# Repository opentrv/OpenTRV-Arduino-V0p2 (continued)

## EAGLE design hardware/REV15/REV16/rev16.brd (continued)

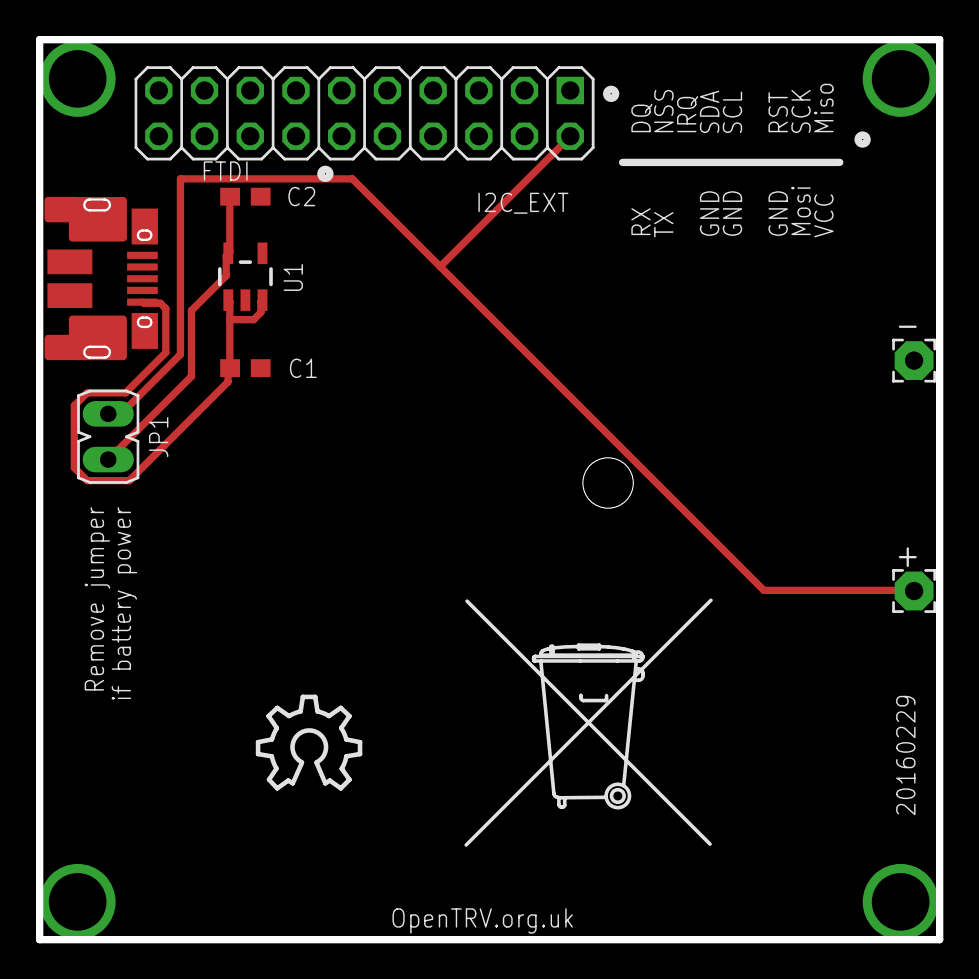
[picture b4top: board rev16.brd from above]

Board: 2 copper layers, 50.0 x 50.0 mm, 10 parts (0 on the bottom side), 4 nets.

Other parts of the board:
U$1: OSHW_10X200_NOTEXT
U$2: TONNE

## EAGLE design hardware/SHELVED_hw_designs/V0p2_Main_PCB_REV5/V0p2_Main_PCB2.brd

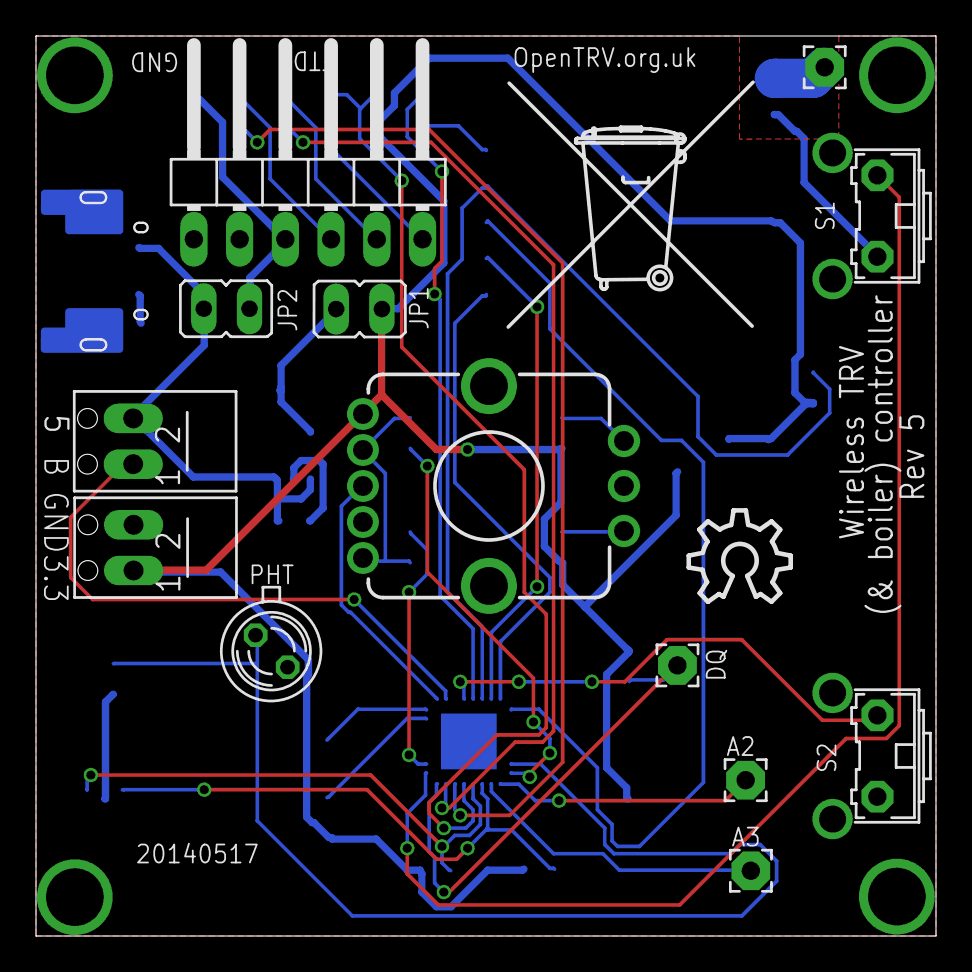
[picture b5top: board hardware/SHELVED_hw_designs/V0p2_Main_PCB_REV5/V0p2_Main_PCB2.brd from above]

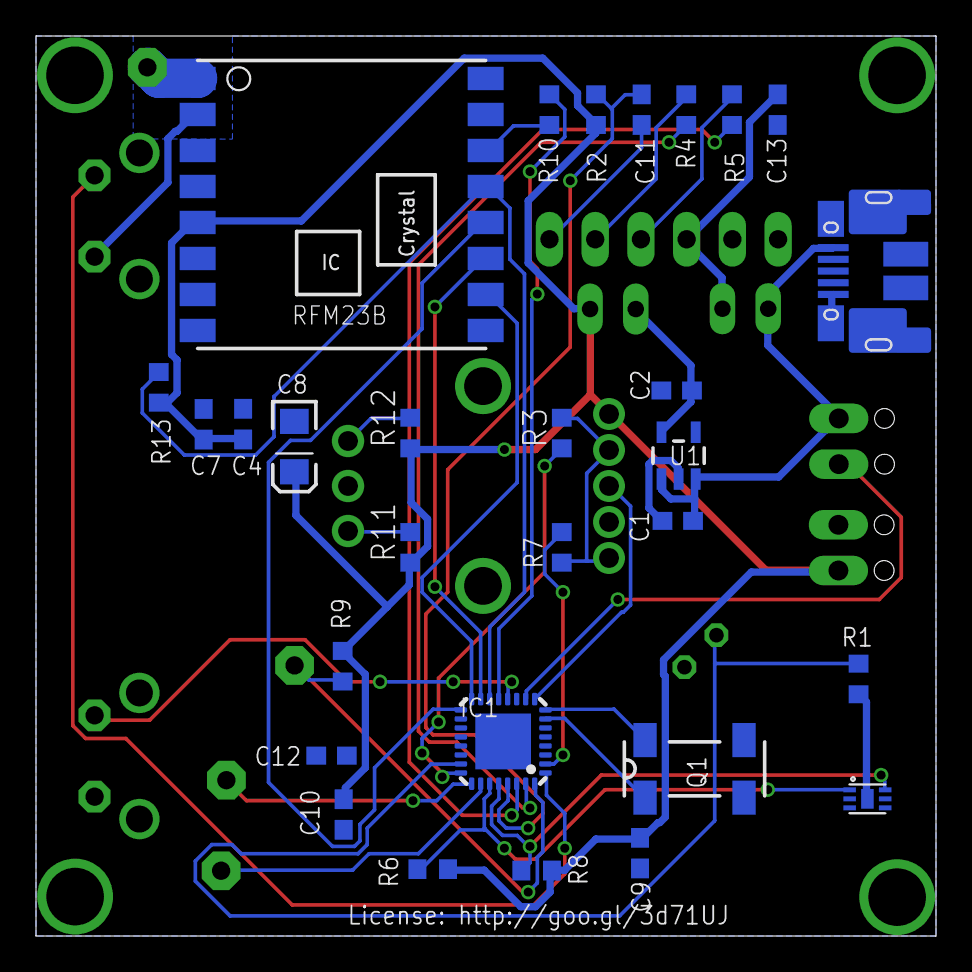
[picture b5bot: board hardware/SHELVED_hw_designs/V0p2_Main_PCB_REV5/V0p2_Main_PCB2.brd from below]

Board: 2 copper layers, 50.0 x 50.0 mm, 44 parts (29 on the bottom side), 37 nets.

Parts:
A2, A3: 2,15/1,0
ANT1: ANT (86 mm); 2,15/1,0
C1, C2, C13: 10uF 10V; C0603
C4: 100pF; C0603
C7, C9, C10, C11, C12: 100nF; C0603
C8: 100uF; EIA3216
DQ: 2,15/1,0
FTDI: 1X06/90
IC1: ATMEGA328-AU; MLF32
JP1, JP2: JP1
PHT: BPX65
Q1: 32768Hz; MC-306
R1: 100K; R0603
R2, R4, R5, R11, R12: 10K; R0603
R3, R7: 470R; R0603
R6, R8: 4K7; R0603
R9: 4.7K; R0603
R10: 1K; R0603
R13: 47K; R0603
RFM23B: RFM23B; RFM23-XXX-S1
S1, S2: B3F-31XX
SW1: ENCODER_LED_3
U1: TC1185SMD; TC1185
U$1: OSHW_10X200_NOTEXT
U$2: TONNE
U$4: SHT21
USBPOWER: MICRO-USB-FCI-10103592
X1, X2: SCREWTERMINAL

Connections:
5V: C1.1, JP2.2, U1.1, U1.3, USBPOWER.1, X1.2
BOILER: IC1.10, X1.1
BUTTON_LEARN2_L: IC1.1, S1.2
BUTTON_LEARN_L: IC1.12, S2.2
BUTTON_MODE_L: IC1.9, SW1.3
D2: DQ.1, IC1.32, R9.1
ENC_A: R11.2, SW1.A
ENC_B: R12.2, SW1.B
GND: C1.2, C2.1, C4.1, C7.2, C8.C, C9.2, C10.2, C12.2, C13.1, FTDI.1, FTDI.2, IC1.3, IC1.21, R1.2, RFM23B.2, RFM23B.9, RFM23B.15, RFM23B.16, S1.1, S2.1, SW1.C, U1.2, U$4.2, U$4.P$1, USBPOWER.5, USBPOWER.7, USBPOWER.17, X2.2
IO_POWER_UP: IC1.11, PHT.K
LDR: IC1.23, PHT.A, R1.1
LED_HEATCALL_B: IC1.24, R3.1
LED_HEATCALL_R: IC1.2, R7.1
unnamed: C11.2, FTDI.6
unnamed: FTDI.4, R5.2
unnamed: FTDI.5, R4.2
unnamed: C12.1, IC1.20
unnamed: R10.2, RFM23B.14
unnamed: C2.2, JP1.1, U1.5
unnamed: C13.2, FTDI.3, JP2.1
unnamed: R3.2, R7.2, SW1.1, SW1.4
unnamed: A2.1, IC1.25
unnamed: A3.1, IC1.26
unnamed: ANT1.1, RFM23B.1
RESET: C11.1, IC1.29, R2.2
RFM_IRQ: IC1.13, R10.1
RX: IC1.31, R4.1
SCL: IC1.28, R8.1, U$4.6
SDA: IC1.27, R6.2, U$4.1
SPI_MISO: IC1.16, RFM23B.10
SPI_MOSI: IC1.15, RFM23B.11
SPI_NSS: IC1.14, R13.1, RFM23B.13
SPI_SCK: IC1.17, RFM23B.12
TX: IC1.30, R5.1
VCC: C4.2, C7.1, C8.A, C9.1, C10.1, IC1.4, IC1.18, JP1.2, R2.1, R6.1, R8.2, R9.2, R11.1, R12.1, R13.2, RFM23B.5, SW1.5, U$4.5, X2.1
XTAL1: IC1.7, Q1.1
XTAL2: IC1.8, Q1.4

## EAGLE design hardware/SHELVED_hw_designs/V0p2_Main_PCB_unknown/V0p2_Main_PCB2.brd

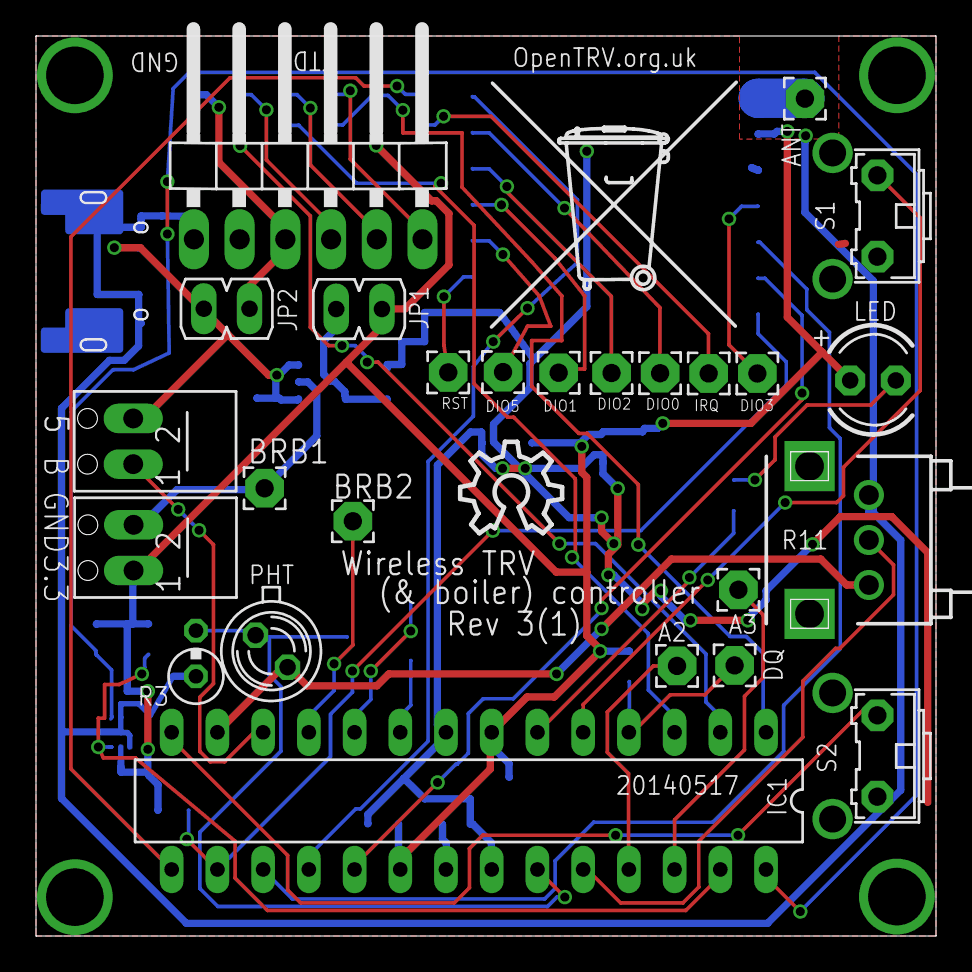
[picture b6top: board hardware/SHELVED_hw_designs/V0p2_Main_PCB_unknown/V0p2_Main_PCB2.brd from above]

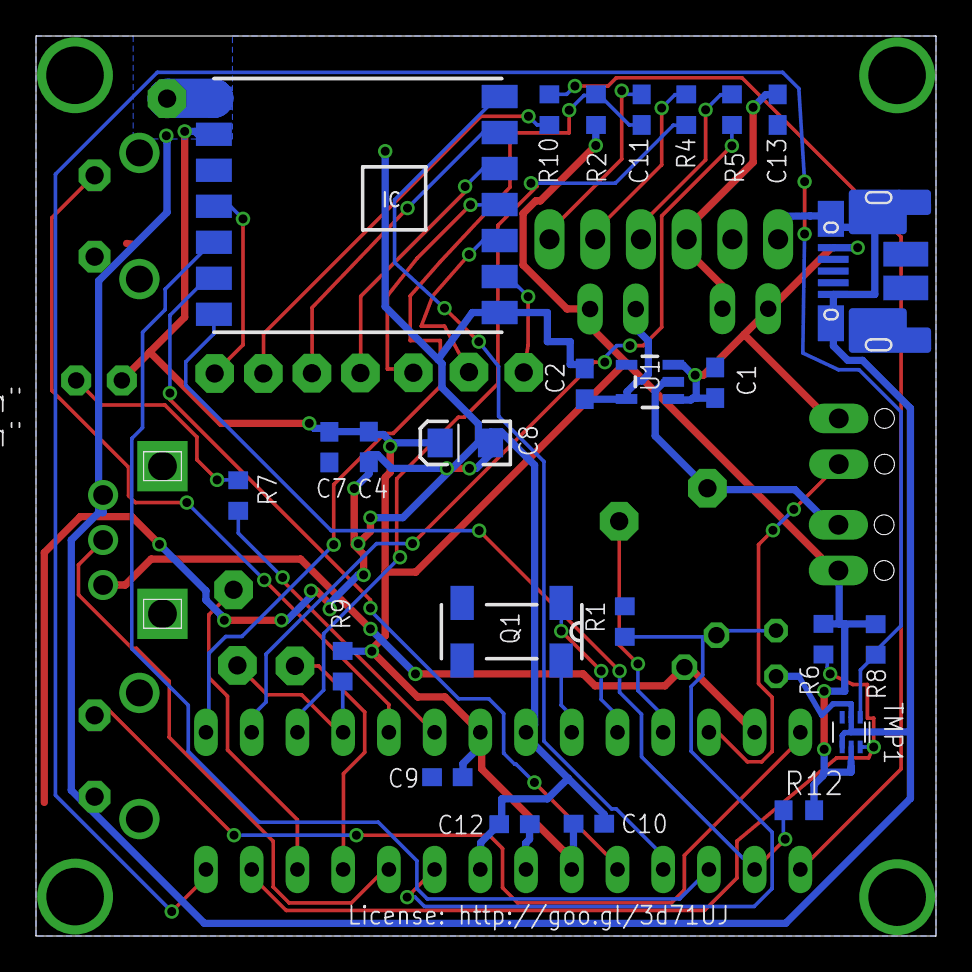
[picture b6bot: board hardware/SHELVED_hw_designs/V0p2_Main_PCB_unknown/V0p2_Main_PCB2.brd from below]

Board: 2 copper layers, 50.0 x 50.0 mm, 52 parts (25 on the bottom side), 41 nets.

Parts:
A2, A3: 2,15/1,0
ANT: ANT (86 mm); 2,15/1,0
BRB1: BRB1; 2,15/1,0
BRB2: BRB2; 2,15/1,0
C1, C2, C13: 10uF 10V; C0603
C4: 100pF; C0603
C7, C9, C10, C11, C12: 100nF; C0603
C8: 100uF; EIA3216
DIO0, DIO1, DIO2, DIO3, DIO5: ANT (86 mm); 2,15/1,0
DQ: 2,15/1,0
FTDI: 1X06/90
IC1: ATMEGA328P-PU; DIL28-3
IRQ: ANT (86 mm); 2,15/1,0
JP1, JP2: JP1
LED: LED3MM
PHT: BPX65
Q1: 32768Hz; MC-306
R1: 100K; R0603
R2, R4, R5: 10K; R0603
R3: 0309V
R6, R8: 4K7; R0603
R7: 470R; R0603
R9: 4.7K; R0603
R10: 1K; R0603
R11: EVUE2A; EVUE
R12: 47K; R0603
RST: ANT (86 mm); 2,15/1,0
S1, S2: B3F-31XX
TMP1: TMP1; TMP112
U1: TC1185SMD; TC1185
U$1: OSHW_10X200_NOTEXT
U$2: TONNE
U$3: RFM69CW; RFM69
USBPOWER: MICRO-USB-FCI-10103592
X1, X2: SCREWTERMINAL

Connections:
5V: C1.1, JP2.2, U1.1, U1.3, USBPOWER.1, X1.2
AI1: IC1.24, R11.2
BOILER: IC1.12, X1.1
BUTTON_LEARN2_L: IC1.5, S1.2
BUTTON_LEARN_L: IC1.14, S2.2
BUTTON_MODE_L: BRB2.1, IC1.11
D2: DQ.1, IC1.4, R9.1
GND: BRB1.1, C1.2, C2.1, C4.2, C7.1, C8.C, C9.2, C10.2, C12.2, C13.1, FTDI.1, FTDI.2, IC1.8, IC1.22, R1.2, R3.1, R11.3, S1.1, S2.1, TMP1.2, TMP1.4, U1.2, U$3.3, U$3.14, USBPOWER.5, USBPOWER.7, USBPOWER.17, X2.2
IO_POWER_UP: IC1.13, PHT.K, R11.1
LDR: IC1.23, PHT.A, R1.1, R3.2
LED_HEATCALL_L: IC1.6, R7.1
unnamed: C11.2, FTDI.6
unnamed: FTDI.4, R5.2
unnamed: FTDI.5, R4.2
unnamed: C12.1, IC1.21
unnamed: IRQ.1, R10.2
unnamed: C2.2, JP1.1, U1.5
unnamed: C13.2, FTDI.3, JP2.1
unnamed: LED.K, R7.2
unnamed: DIO0.1, U$3.9
unnamed: DIO2.1, U$3.10
unnamed: DIO1.1, U$3.11
unnamed: DIO5.1, U$3.12
unnamed: RST.1, U$3.13
unnamed: DIO3.1, U$3.4
unnamed: A2.1, IC1.25
unnamed: A3.1, IC1.26
unnamed: ANT.1, U$3.1
RESET: C11.1, IC1.1, R2.2
RFM_IRQ: IC1.15, R10.1
RX: IC1.3, R4.1
SCL: IC1.28, R8.1, TMP1.1
SDA: IC1.27, R6.2, TMP1.6
SPI_MISO: IC1.18, U$3.8
SPI_MOSI: IC1.17, U$3.5
SPI_NSS: IC1.16, R12.1, U$3.7
SPI_SCK: IC1.19, U$3.6
TX: IC1.2, R5.1
VCC: C4.1, C7.2, C8.A, C9.1, C10.1, IC1.7, IC1.20, JP1.2, LED.A, R2.1, R6.1, R8.2, R9.2, R12.2, TMP1.5, U$3.2, X2.1
XTAL1: IC1.9, Q1.4
XTAL2: IC1.10, Q1.1

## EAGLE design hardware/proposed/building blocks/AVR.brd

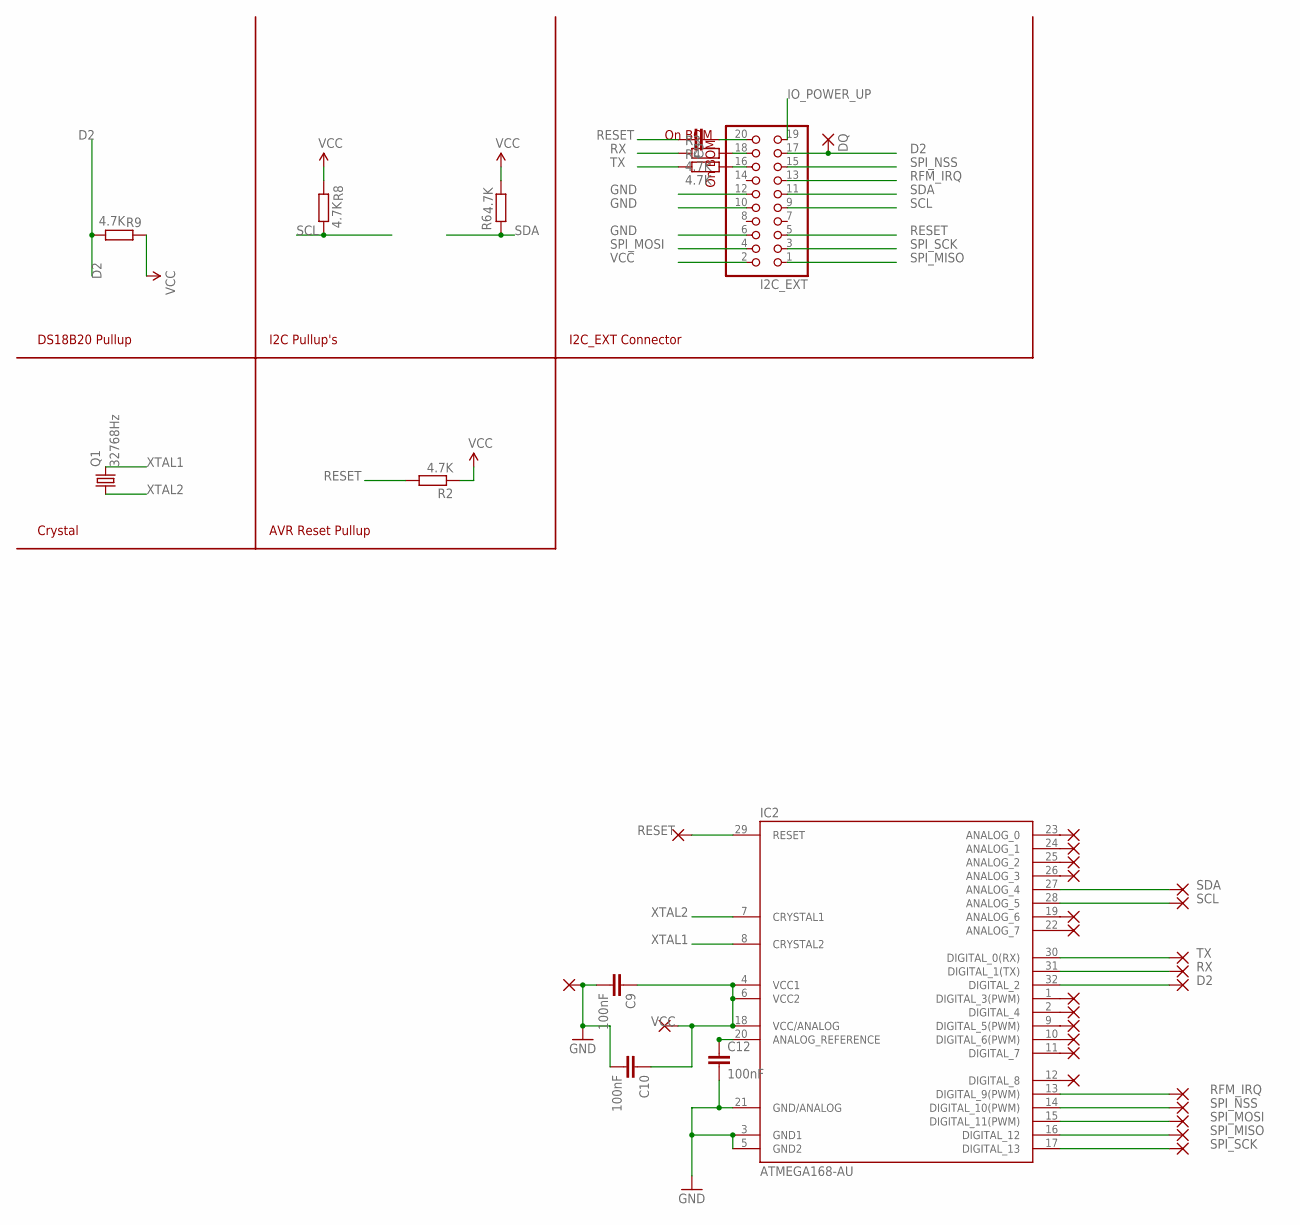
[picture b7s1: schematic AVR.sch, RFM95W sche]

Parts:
C5, C9, C10, C12: 100nF; C0603
DQ: 2,15/1,0
I2C_EXT: PINHD-2X10; 2X10
IC2: ATMEGA168-AU; TQFP32-08
PAD1, PAD2, PAD3, PAD4, PAD5, PAD6, PAD7, PAD8, PAD9, PAD10, PAD11, PAD12, PAD13, PAD14, PAD15, PAD16, PAD17, PAD18, PAD19, PAD20, PAD21, PAD22, PAD23, PAD24, PAD25: 1,6/0,8
Q1: 32768Hz; MC-306
R2, R3, R4, R6, R8, R9: 4.7K; R0603

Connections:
D2: DQ.1, I2C_EXT.17, IC2.32 (DIGITAL_2), PAD14.1, R9.1
GND: C9.2, C10.2, C12.2, I2C_EXT.6, I2C_EXT.10, I2C_EXT.12, IC2.3 (GND1), IC2.5 (GND2), IC2.21 (GND/ANALOG), PAD2.1
IO_POWER_UP: I2C_EXT.19
unnamed: I2C_EXT.18, R3.2
unnamed: IC2.23 (ANALOG_0), PAD4.1
unnamed: I2C_EXT.16, R4.2
unnamed: C5.2, I2C_EXT.20
unnamed: IC2.24 (ANALOG_1), PAD5.1
unnamed: C12.1, IC2.20 (ANALOG_REFERENCE)
unnamed: IC2.25 (ANALOG_2), PAD6.1
unnamed: IC2.19 (ANALOG_6), PAD10.1
unnamed: IC2.1 (DIGITAL_3(PWM)), PAD15.1
unnamed: IC2.2 (DIGITAL_4), PAD16.1
unnamed: IC2.9 (DIGITAL_5(PWM)), PAD17.1
unnamed: IC2.10 (DIGITAL_6(PWM)), PAD18.1
unnamed: IC2.11 (DIGITAL_7), PAD19.1
unnamed: IC2.26 (ANALOG_3), PAD7.1
unnamed: IC2.22 (ANALOG_7), PAD11.1
unnamed: IC2.12 (DIGITAL_8), PAD20.1
RESET: C5.1, I2C_EXT.5, IC2.29 (RESET), PAD1.1, R2.2
RFM_IRQ: I2C_EXT.13, IC2.13 (DIGITAL_9(PWM)), PAD21.1
RX: IC2.31 (DIGITAL_1(TX)), PAD13.1, R3.1
SCL: I2C_EXT.9, IC2.28 (ANALOG_5), PAD9.1, R8.1
SDA: I2C_EXT.11, IC2.27 (ANALOG_4), PAD8.1, R6.2
SPI_MISO: I2C_EXT.1, IC2.16 (DIGITAL_12), PAD24.1
SPI_MOSI: I2C_EXT.4, IC2.15 (DIGITAL_11(PWM)), PAD23.1
SPI_NSS: I2C_EXT.15, IC2.14 (DIGITAL_10(PWM)), PAD22.1
SPI_SCK: I2C_EXT.3, IC2.17 (DIGITAL_13), PAD25.1
TX: IC2.30 (DIGITAL_0(RX)), PAD12.1, R4.1
VCC: C9.1, C10.1, I2C_EXT.2, IC2.4 (VCC1), IC2.6 (VCC2), IC2.18 (VCC/ANALOG), PAD3.1, R2.1, R6.1, R8.2, R9.2
XTAL1: IC2.8 (CRYSTAL2), Q1.4 (2)
XTAL2: IC2.7 (CRYSTAL1), Q1.1

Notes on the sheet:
On BOM
Crystal
AVR Reset Pullup
DS18B20 Pullup
I2C_EXT Connector
I2C Pullup's

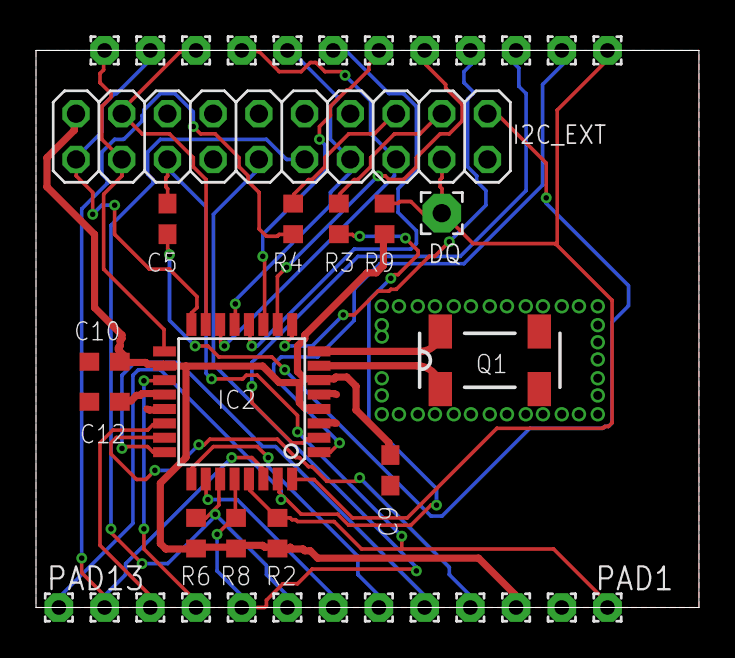
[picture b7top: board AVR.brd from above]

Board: 2 copper layers, 36.8 x 30.9 mm, 39 parts (0 on the bottom side), 31 nets.
